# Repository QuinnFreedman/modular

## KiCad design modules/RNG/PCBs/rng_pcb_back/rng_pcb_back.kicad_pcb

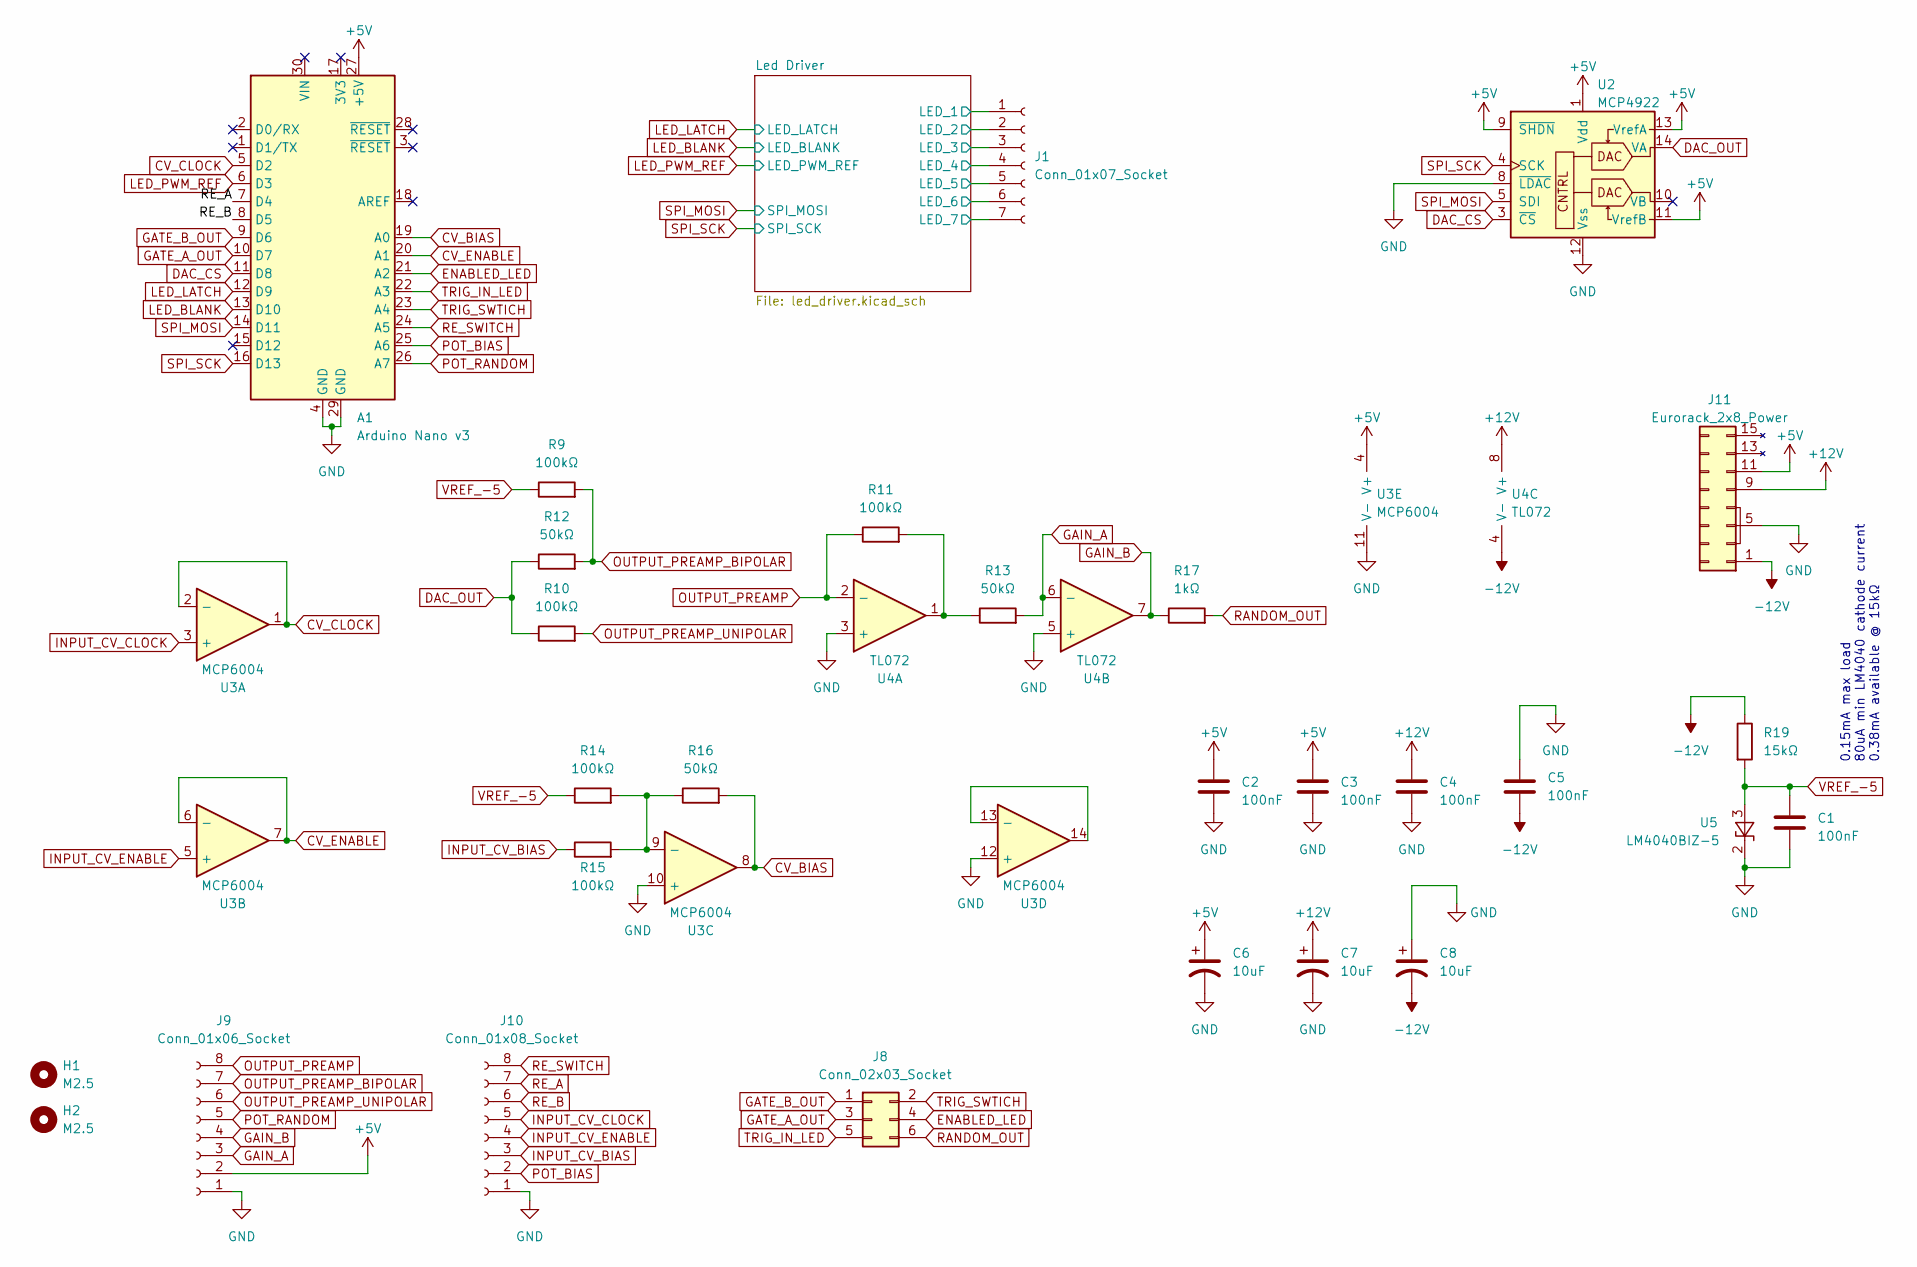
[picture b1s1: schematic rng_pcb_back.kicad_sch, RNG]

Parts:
A1: Arduino Nano v3; Arduino_Nano
C1, C2, C3, C4, C5: 100nF; C_Disc_D5.0mm_W2.5mm_P5.00mm
C6, C7, C8: 10uF; CP_Radial_D4.0mm_P1.50mm
H1, H2: M2.5; MountingHole_2.7mm_M2.5
J1: Conn_01x07_Socket; PinHeader_1x07_P2.54mm_Vertical
J8: Conn_02x03_Socket; PinHeader_2x03_P2.54mm_Vertical
J9: Conn_01x06_Socket; PinHeader_1x08_P2.54mm_Vertical
J10: Conn_01x08_Socket; PinHeader_1x08_P2.54mm_Vertical
J11: Eurorack_2x8_Power; IDC-Header_2x08_P2.54mm_Vertical
R9, R10, R11, R14, R15: 100kΩ; R_Axial_DIN0207_L6.3mm_D2.5mm_P7.62mm_Horizontal
R12, R13, R16: 50kΩ; R_Axial_DIN0207_L6.3mm_D2.5mm_P7.62mm_Horizontal
R17: 1kΩ; R_Axial_DIN0207_L6.3mm_D2.5mm_P7.62mm_Horizontal
R19: 15kΩ; R_Axial_DIN0207_L6.3mm_D2.5mm_P7.62mm_Horizontal
U2: MCP4922; DIP-14_W7.62mm
U3: MCP6004; DIP-14_W7.62mm
U4: TL072; DIP-8_W7.62mm
U5: LM4040BIZ-5; TO-92_Inline_Wide

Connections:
+5V: A1.27 (+5V), C2.1, C3.1, C6.1, J9.2, J11.11 (+5v), J11.12 (+5v), U2.1 (Vdd), U2.9 (~SHDN), U2.11 (VrefB), U2.13 (VrefA), U3.4 (V+); also elsewhere on the board
+12V: C4.1, C7.1, J11.9 (+12v), J11.10 (+12v), U4.8 (V+)
-12V: C5.2, C8.2, J11.1 (-12v), J11.2 (-12v), R19.1, U4.4 (V-)
/Led Driver/LED_1: J1.1; also elsewhere on the board
/Led Driver/LED_2: J1.2; also elsewhere on the board
/Led Driver/LED_3: J1.3; also elsewhere on the board
/Led Driver/LED_4: J1.4; also elsewhere on the board
/Led Driver/LED_5: J1.5; also elsewhere on the board
/Led Driver/LED_6: J1.6; also elsewhere on the board
/Led Driver/LED_7: J1.7; also elsewhere on the board
CV_BIAS: A1.19 (A0), R16.2, U3.8
CV_CLOCK: A1.5 (D2), U3.1, U3.2 (-)
CV_ENABLE: A1.20 (A1), U3.6 (-), U3.7
DAC_CS: A1.11 (D8), U2.3 (~CS)
DAC_OUT: R10.1, R12.1, U2.14 (VA)
ENABLED_LED: A1.21 (A2), J8.4
GAIN_A: J9.3, R13.2, U4.6 (-)
GAIN_B: J9.4, R17.1, U4.7
GATE_A_OUT: A1.10 (D7), J8.3
GATE_B_OUT: A1.9 (D6), J8.1
GND: A1.4 (GND), A1.29 (GND), C1.2, C2.2, C3.2, C4.2, C5.1, C6.2, C7.2, C8.1, J9.1, J10.1, J11.3 (GND), J11.4 (GND), J11.5 (GND), J11.6 (GND), J11.7 (GND), J11.8 (GND), U2.8 (~LDAC), U2.12 (Vss), U3.10 (+), U3.11 (V-), U3.12 (+), U4.3 (+), U4.5 (+), U5.2 (K); also elsewhere on the board
INPUT_CV_BIAS: J10.3, R15.1
INPUT_CV_CLOCK: J10.5, U3.3 (+)
INPUT_CV_ENABLE: J10.4, U3.5 (+)
LED_BLANK: A1.13 (D10); also elsewhere on the board
LED_LATCH: A1.12 (D9); also elsewhere on the board
LED_PWM_REF: A1.6 (D3); also elsewhere on the board
unnamed: R11.2, R13.1, U4.1
unnamed: R14.2, R15.2, R16.1, U3.9 (-)
unnamed: U3.13 (-), U3.14
OUTPUT_PREAMP: J9.8, R11.1, U4.2 (-)
OUTPUT_PREAMP_BIPOLAR: J9.7, R9.2, R12.2
OUTPUT_PREAMP_UNIPOLAR: J9.6, R10.2
POT_BIAS: A1.25 (A6), J10.2
POT_RANDOM: A1.26 (A7), J9.5
RANDOM_OUT: J8.6, R17.2
RE_A: A1.7 (D4), J10.7
RE_B: A1.8 (D5), J10.6
RE_SWITCH: A1.24 (A5), J10.8
SPI_MOSI: A1.14 (D11), U2.5 (SDI); also elsewhere on the board
SPI_SCK: A1.16 (D13), U2.4 (SCK); also elsewhere on the board
TRIG_IN_LED: A1.22 (A3), J8.5
TRIG_SWTICH: A1.23 (A4), J8.2
VREF_-5: C1.1, R9.1, R14.1, R19.2, U5.3 (A)

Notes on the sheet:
0.15mA max load 80uA min LM4040 cathode current 0.38mA available @ 15kΩ

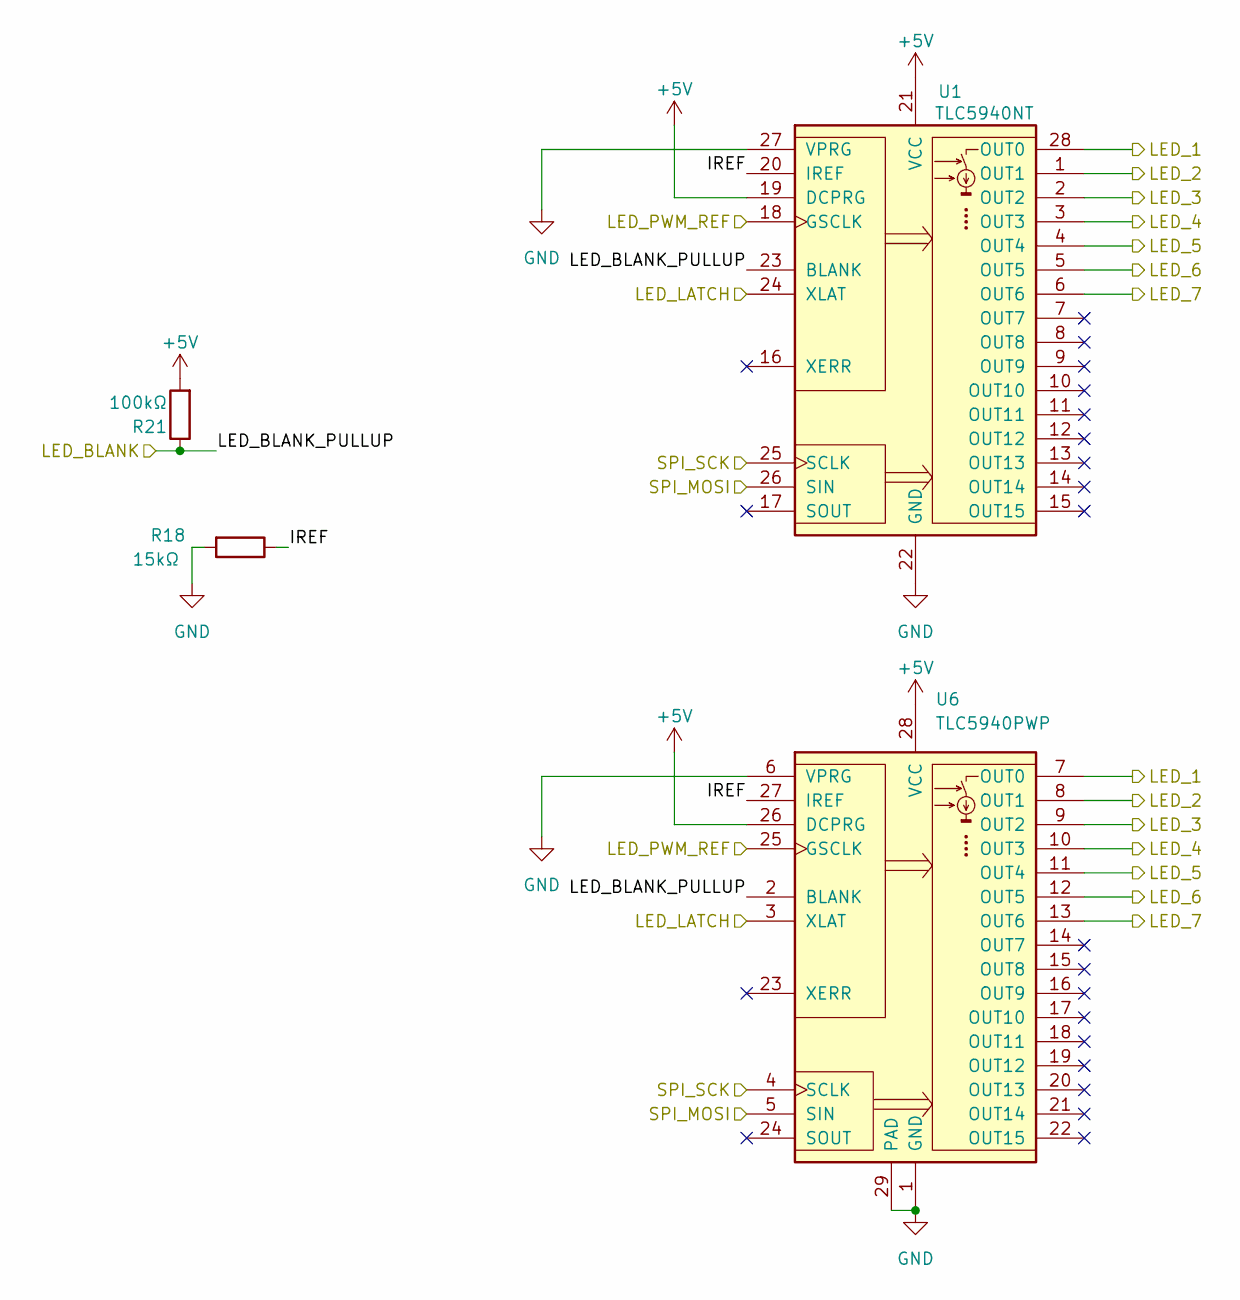
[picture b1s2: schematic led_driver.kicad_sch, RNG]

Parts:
R18: 15kΩ; R_Axial_DIN0207_L6.3mm_D2.5mm_P7.62mm_Horizontal
R21: 100kΩ; R_Axial_DIN0207_L6.3mm_D2.5mm_P7.62mm_Horizontal
U1: TLC5940NT; DIP-28_W7.62mm
U6: TLC5940PWP; HTSSOP-28-1EP_4.4x9.7mm_P0.65mm_EP3.4x9.5mm_Mask2.4x6.17mm_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

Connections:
+5V: R21.2, U1.19 (DCPRG), U1.21 (VCC), U6.26 (DCPRG), U6.28 (VCC); also elsewhere on the board
/Led Driver/IREF: R18.1, U1.20 (IREF), U6.27 (IREF)
/Led Driver/LED_1: U1.28 (OUT0), U6.7 (OUT0); also elsewhere on the board
/Led Driver/LED_2: U1.1 (OUT1), U6.8 (OUT1); also elsewhere on the board
/Led Driver/LED_3: U1.2 (OUT2), U6.9 (OUT2); also elsewhere on the board
/Led Driver/LED_4: U1.3 (OUT3), U6.10 (OUT3); also elsewhere on the board
/Led Driver/LED_5: U1.4 (OUT4), U6.11 (OUT4); also elsewhere on the board
/Led Driver/LED_6: U1.5 (OUT5), U6.12 (OUT5); also elsewhere on the board
/Led Driver/LED_7: U1.6 (OUT6), U6.13 (OUT6); also elsewhere on the board
GND: R18.2, U1.22 (GND), U1.27 (VPRG), U6.1 (GND), U6.6 (VPRG), U6.29 (PAD); also elsewhere on the board
LED_BLANK: R21.1, U1.23 (BLANK), U6.2 (BLANK); also elsewhere on the board
LED_LATCH: U1.24 (XLAT), U6.3 (XLAT); also elsewhere on the board
LED_PWM_REF: U1.18 (GSCLK), U6.25 (GSCLK); also elsewhere on the board
SPI_MOSI: U1.26 (SIN), U6.5 (SIN); also elsewhere on the board
SPI_SCK: U1.25 (SCLK), U6.4 (SCLK); also elsewhere on the board

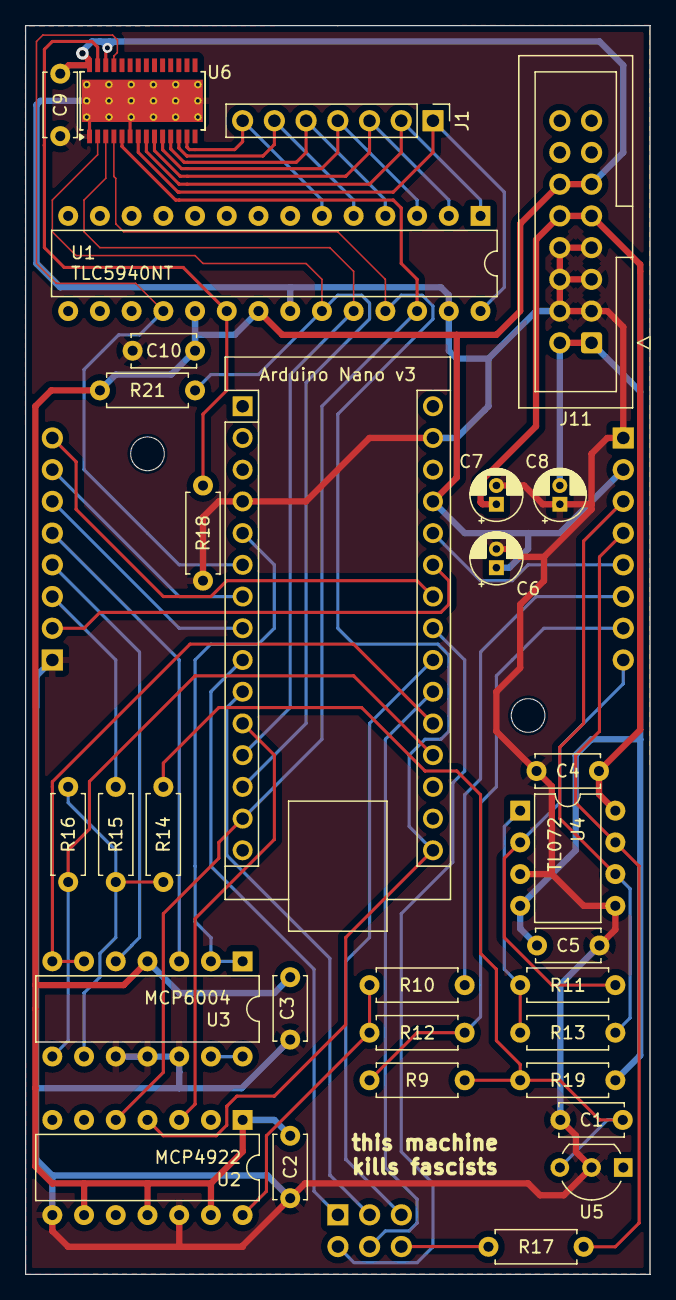
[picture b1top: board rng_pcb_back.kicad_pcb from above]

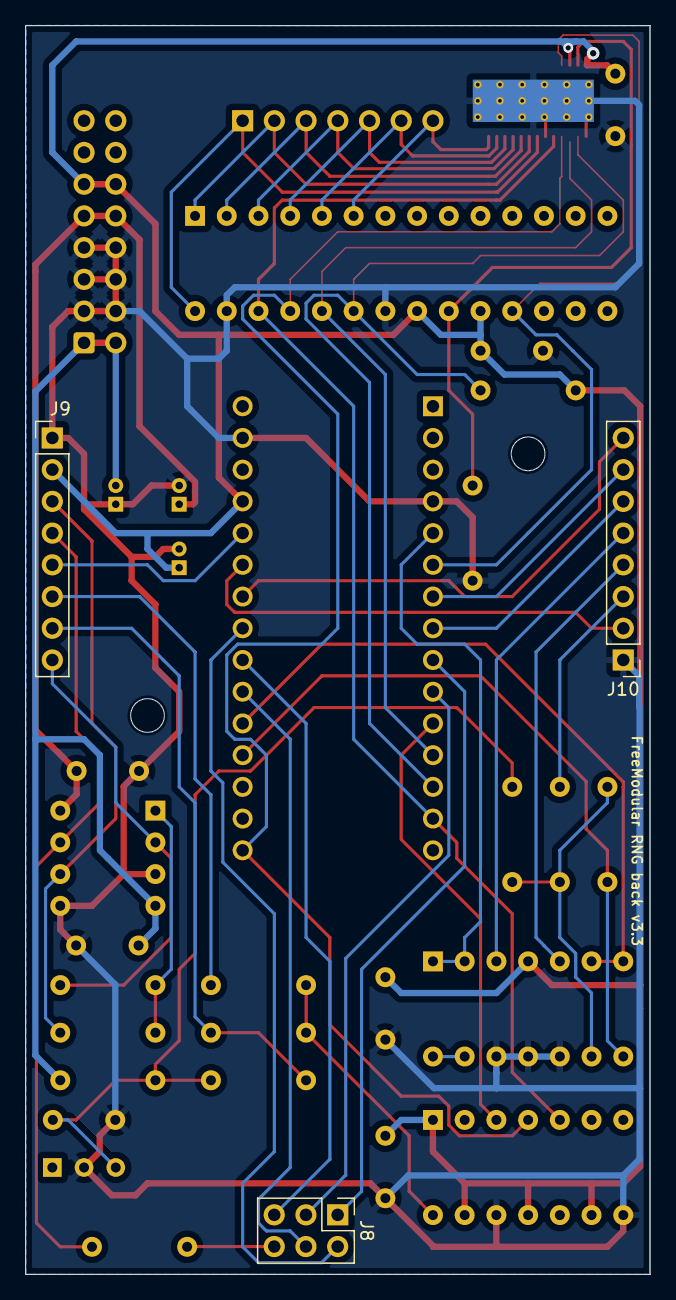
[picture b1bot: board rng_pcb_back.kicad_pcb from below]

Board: 2 copper layers, 50.0 x 100.0 mm, 36 parts (3 on the bottom side), 45 nets.

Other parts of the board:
C9, C10: 100nF; C_Disc_D5.0mm_W2.5mm_P5.00mm

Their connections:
+5V: C9.1, C10.1; also elsewhere on the board
GND: C9.2, C10.2; also elsewhere on the board

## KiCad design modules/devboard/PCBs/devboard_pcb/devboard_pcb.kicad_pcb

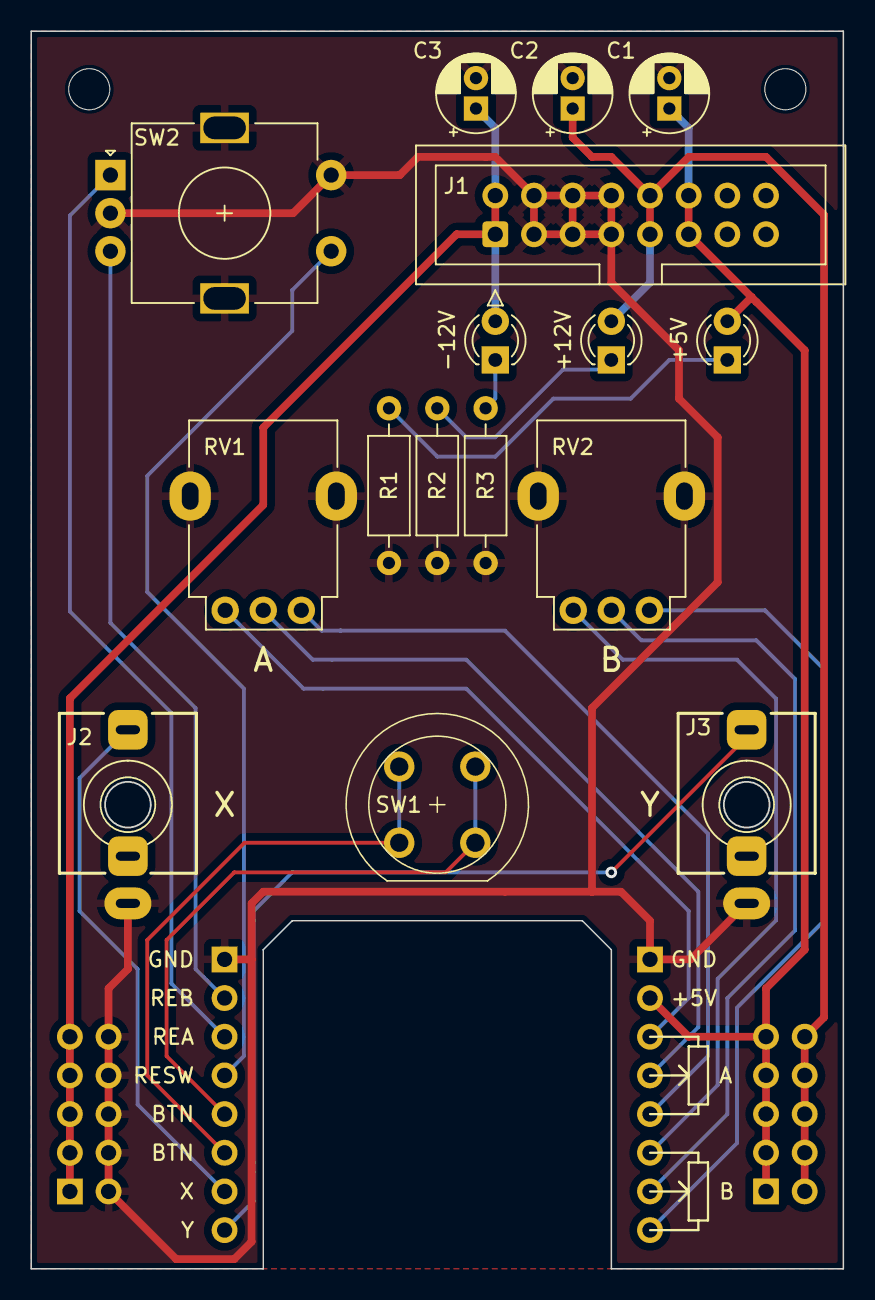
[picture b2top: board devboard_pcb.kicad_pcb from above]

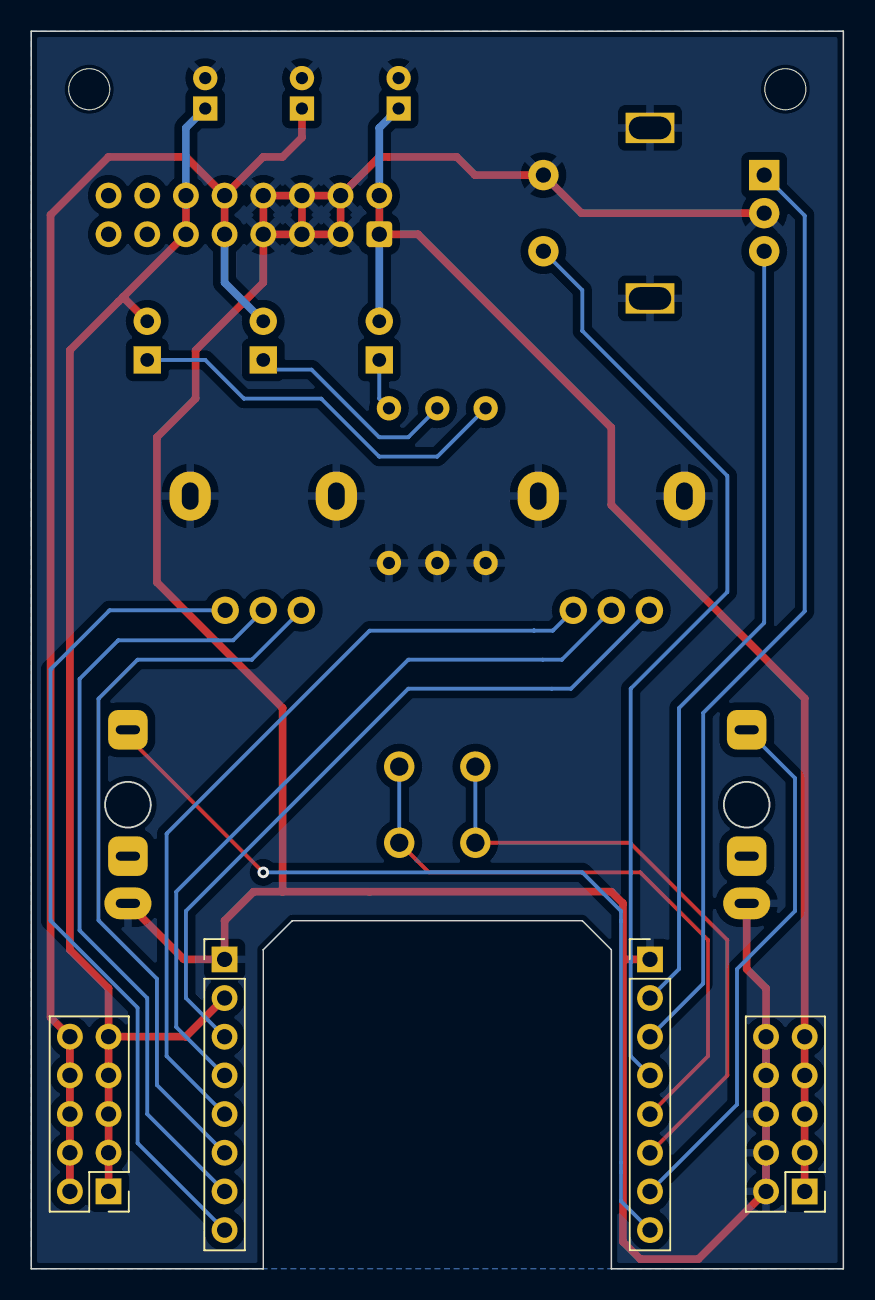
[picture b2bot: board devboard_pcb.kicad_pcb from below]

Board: 2 copper layers, 53.3 x 81.3 mm, 22 parts (4 on the bottom side), 20 nets.

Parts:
C1, C2, C3: 10uF; CP_Radial_D5.0mm_P2.00mm
D1, D2, D3: LED; LED_D3.0mm
H1, H2: MountingHole; MountingHole_2.7mm_M2.5
J1: Eurorack_2x8_Power; IDC-Header_2x08_P2.54mm_Vertical
J2, J3: THONKICONN
J4, J5: Conn_01x08_Pin; PinHeader_1x08_P2.54mm_Vertical
J6, J7: Conn_02x05_Top_Bottom; PinHeader_2x05_P2.54mm_Vertical
R1, R2, R3: R; R_Axial_DIN0207_L6.3mm_D2.5mm_P10.16mm_Horizontal
RV1, RV2: R_Potentiometer; Alpha_Potentiometer_Grounded
SW1: SW_SPST; D6R
SW2: RotaryEncoder_Switch; RotaryEncoder_Alps_EC11E-Switch_Vertical_H20mm

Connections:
+5V: C1.1, D1.2 (A), J1.11 (+5v), J1.12 (+5v), J4.2, J7.1, J7.3, J7.5, J7.7, J7.9
+12V: C2.1, D2.2 (A), J1.9 (+12v), J1.10 (+12v), J7.2, J7.4, J7.6, J7.8, J7.10
-12V: C3.1, D3.2 (A), J1.1 (-12v), J1.2 (-12v), J6.1, J6.3, J6.5, J6.7, J6.9
GND: C1.2, C2.2, C3.2, J1.3 (GND), J1.4 (GND), J1.5 (GND), J1.6 (GND), J1.7 (GND), J1.8 (GND), J2.1, J3.1, J4.1, J5.1, J6.2, J6.4, J6.6, J6.8, J6.10, R1.2, R2.2, R3.2, RV1.MP, RV2.MP, SW2.C, SW2.MP, SW2.S2
unnamed: D1.1 (K), R1.1
unnamed: D2.1 (K), R2.1
unnamed: D3.1 (K), R3.1
unnamed: J4.3, RV1.1
unnamed: J4.4, RV1.2
unnamed: J4.5, RV1.3
unnamed: J4.6, RV2.1
unnamed: J4.7, RV2.2
unnamed: J4.8, RV2.3
unnamed: J5.2, SW2.B
unnamed: J5.3, SW2.A
unnamed: J5.4, SW2.S1
unnamed: J5.5, SW1.2 (B)
unnamed: J5.6, SW1.1 (A)
unnamed: J2.3, J5.7
unnamed: J3.3, J5.8

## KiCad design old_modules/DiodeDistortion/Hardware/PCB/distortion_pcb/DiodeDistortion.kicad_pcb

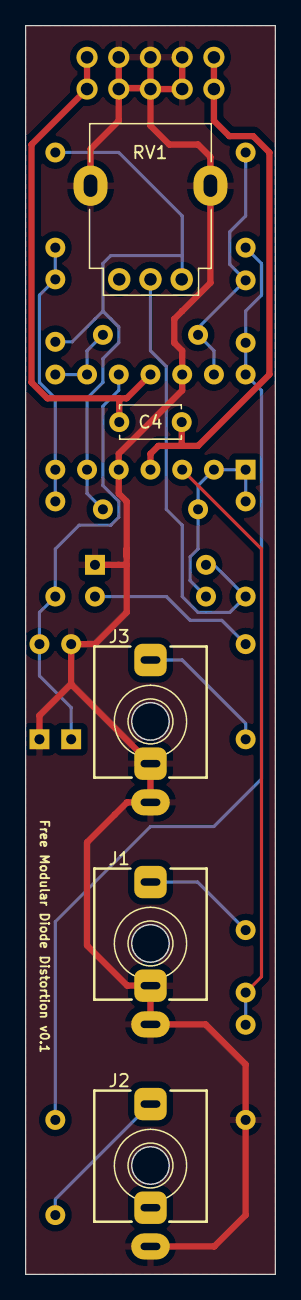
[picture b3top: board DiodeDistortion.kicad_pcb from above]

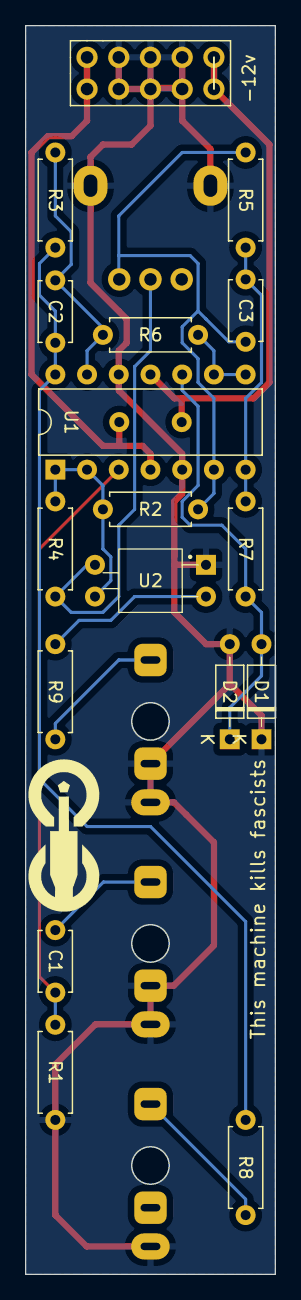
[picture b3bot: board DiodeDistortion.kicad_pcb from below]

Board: 2 copper layers, 20.0 x 100.0 mm, 22 parts (17 on the bottom side), 16 nets.

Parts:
C1: 1uF; C_Disc_D4.7mm_W2.5mm_P5.00mm
C2, C3: 100pF; C_Disc_D4.7mm_W2.5mm_P5.00mm
C4: 100nF; C_Disc_D4.7mm_W2.5mm_P5.00mm
D1, D2: 1N4148; D_DO-35_SOD27_P7.62mm_Horizontal
J1, J2, J3: THONKICONN
J4: Conn_01x10_Pin; PinSocket_2x05_P2.54mm_Vertical
R1, R2, R3: 100k; R_Axial_DIN0207_L6.3mm_D2.5mm_P7.62mm_Horizontal
R4, R5, R6, R7: 10k; R_Axial_DIN0207_L6.3mm_D2.5mm_P7.62mm_Horizontal
R8, R9: 1k; R_Axial_DIN0207_L6.3mm_D2.5mm_P7.62mm_Horizontal
RV1: 100k; Alpha_Potentiometer_Grounded
U1: TL074; DIP-14_W7.62mm
U2: NSL-32

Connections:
+12V: C4.1, J4.1, J4.2, U1.4 (V+)
-12V: C4.2, J4.9, J4.10, U1.11 (V-)
GND: D1.1 (K), D2.2 (A), J1.1, J1.2, J2.1, J3.1, J3.2, J4.3, J4.4, J4.5, J4.6, J4.7, J4.8, R1.2, RV1.MP, U1.5 (+), U1.12 (+), U2.2
unnamed: C1.1, J1.3
unnamed: C2.2, R3.2, R8.1, U1.14
unnamed: C3.2, R5.2, R7.1, U1.7
unnamed: D1.2 (A), D2.1 (K), R7.2, U1.10 (+)
unnamed: J2.3, R8.2
unnamed: J3.3, R9.1
unnamed: R4.2, RV1.2, U2.3
unnamed: R9.2, U2.1
unnamed: C1.2, R1.1, U1.3 (+)
unnamed: R2.1, R4.1, U1.1, U1.2 (-), U2.4
unnamed: C3.1, R2.2, R5.1, RV1.3, U1.6 (-)
unnamed: R6.1, U1.8, U1.9 (-)
unnamed: C2.1, R3.1, R6.2, U1.13 (-)

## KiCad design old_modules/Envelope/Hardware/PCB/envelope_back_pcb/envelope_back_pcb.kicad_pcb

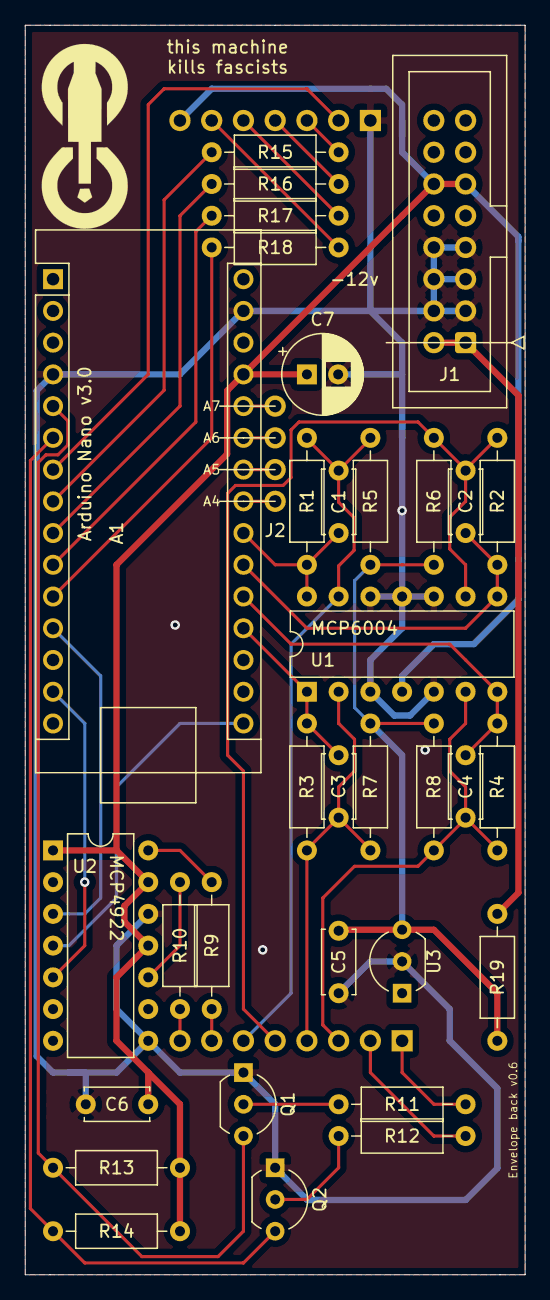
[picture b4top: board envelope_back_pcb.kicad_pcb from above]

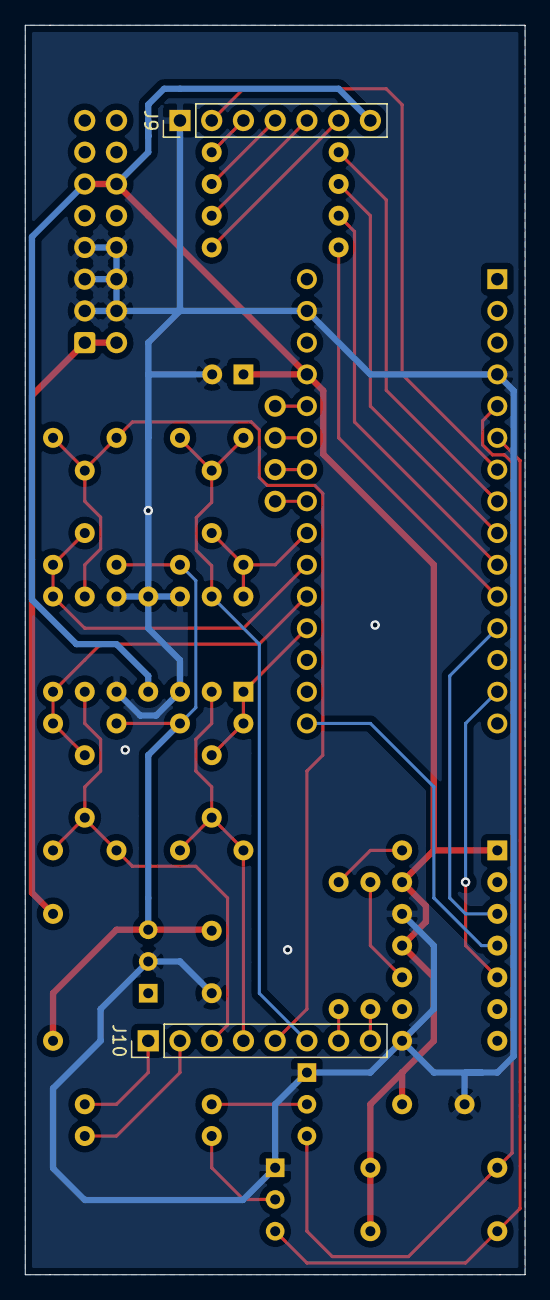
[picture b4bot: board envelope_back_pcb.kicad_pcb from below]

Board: 2 copper layers, 40.0 x 100.0 mm, 36 parts (2 on the bottom side), 39 nets.

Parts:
A1: Arduino_Nano_v3.x; Arduino_Nano
C1, C2, C3, C4: 10nF; C_Disc_D5.0mm_W2.5mm_P5.00mm
C5, C6: 100nF; C_Disc_D5.0mm_W2.5mm_P5.00mm
C7: 10uF; CP_Radial_D6.3mm_P2.50mm
J1: Conn_02x08_Odd_Even; IDC-Header_2x08_P2.54mm_Vertical
J2: Conn_01x04_Female; PinHeader_1x04_P2.54mm_Vertical
J9: Conn_01x07_Male; PinHeader_1x07_P2.54mm_Vertical
J10: Conn_01x08_Male; PinHeader_1x08_P2.54mm_Vertical
Q1, Q2: 2N3904; TO-92_Inline_Wide
R1, R2, R3, R4, R5, R6, R7, R8: 100kΩ; R_Axial_DIN0207_L6.3mm_D2.5mm_P10.16mm_Horizontal
R9, R10: 1kΩ; R_Axial_DIN0207_L6.3mm_D2.5mm_P10.16mm_Horizontal
R11, R12, R13, R14: 10kΩ; R_Axial_DIN0207_L6.3mm_D2.5mm_P10.16mm_Horizontal
R15, R16, R17, R18: 5.1kΩ; R_Axial_DIN0207_L6.3mm_D2.5mm_P10.16mm_Horizontal
R19: 470Ω; R_Axial_DIN0207_L6.3mm_D2.5mm_P10.16mm_Horizontal
U1: MCP6004; DIP-14_W7.62mm
U2: MCP4922; DIP-14_W7.62mm
U3: LM4040LP-5; TO-92_Inline_Wide

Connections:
+5V: A1.27, C6.1, C7.1, J1.11, J1.12, J9.7, R13.1, R14.1, U1.4, U2.1, U2.11, U2.13
+12V: J1.9, J1.10
-5v_REF: C5.2, R5.2, R6.2, R7.2, R8.2, R19.1, U3.3
-12V: J1.1, J1.2, R19.2
BUTTON: A1.7, J9.2
CV_1: C1.2, J10.6, R1.2, R5.1, U1.13
CV_1_5v: A1.22, C1.1, R1.1, U1.14
CV_2: C2.2, J10.5, R2.2, R6.1, U1.9
CV_2_5v: A1.21, C2.1, R2.1, U1.8
CV_3: C3.2, J10.4, R3.2, R7.1, U1.2
CV_3_5v: A1.19, C3.1, R3.1, U1.1
CV_4: C4.2, J10.3, R4.2, R8.1, U1.6
CV_4_5v: A1.20, C4.1, R4.1, U1.7
DAC_CS: A1.12, U2.3
GATE_IN: J10.1, R11.2
GATE_IN_5v: A1.5, Q1.3, R13.2
GND: A1.4, A1.29, C5.1, C6.2, C7.2, J1.3, J1.4, J1.5, J1.6, J1.7, J1.8, J9.1, Q1.1, Q2.1, U1.3, U1.5, U1.10, U1.11, U1.12, U2.8, U2.12, U3.2
LED_1: J9.3, R15.2
LED_2: J9.4, R16.2
LED_3: J9.5, R17.2
LED_4: J9.6, R18.2
unnamed: A1.8, R15.1
unnamed: A1.9, R16.1
unnamed: A1.10, R17.1
unnamed: A1.11, R18.1
unnamed: A1.23, J2.1
unnamed: A1.24, J2.2
unnamed: A1.25, J2.3
unnamed: A1.26, J2.4
unnamed: Q1.2, R11.1
unnamed: Q2.2, R12.1
unnamed: R9.2, U2.14
unnamed: R10.2, U2.10
OUT: J10.7, R9.1
OUT_INV: J10.8, R10.1
SPI_MOSI: A1.14, U2.5
SPI_SCK: A1.16, U2.4
TRIG_IN: J10.2, R12.2
TRIG_IN_5v: A1.6, Q2.3, R14.2
